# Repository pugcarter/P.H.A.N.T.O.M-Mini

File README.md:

# P.H.A.N.T.O.M-Mini

https://cad.onshape.com/documents/66c52b2957eb4a6fa7516106/w/d311932d626167deb0beda08/e/a58703558c87bdbf4c51b0a4

The P.H.A.N.T.O.M Mini is a samll ghost hunting phone P. paranormal H. Hunting A. Analize N. navigation T: Tracking O,M. Obersvation Machine me and my friends intend on going to a real hunated school Having a touchscreen with emf heartrate temp sensors I plan on maybe having detacble cameras and a walking survalnce drone with sonar and heat camera

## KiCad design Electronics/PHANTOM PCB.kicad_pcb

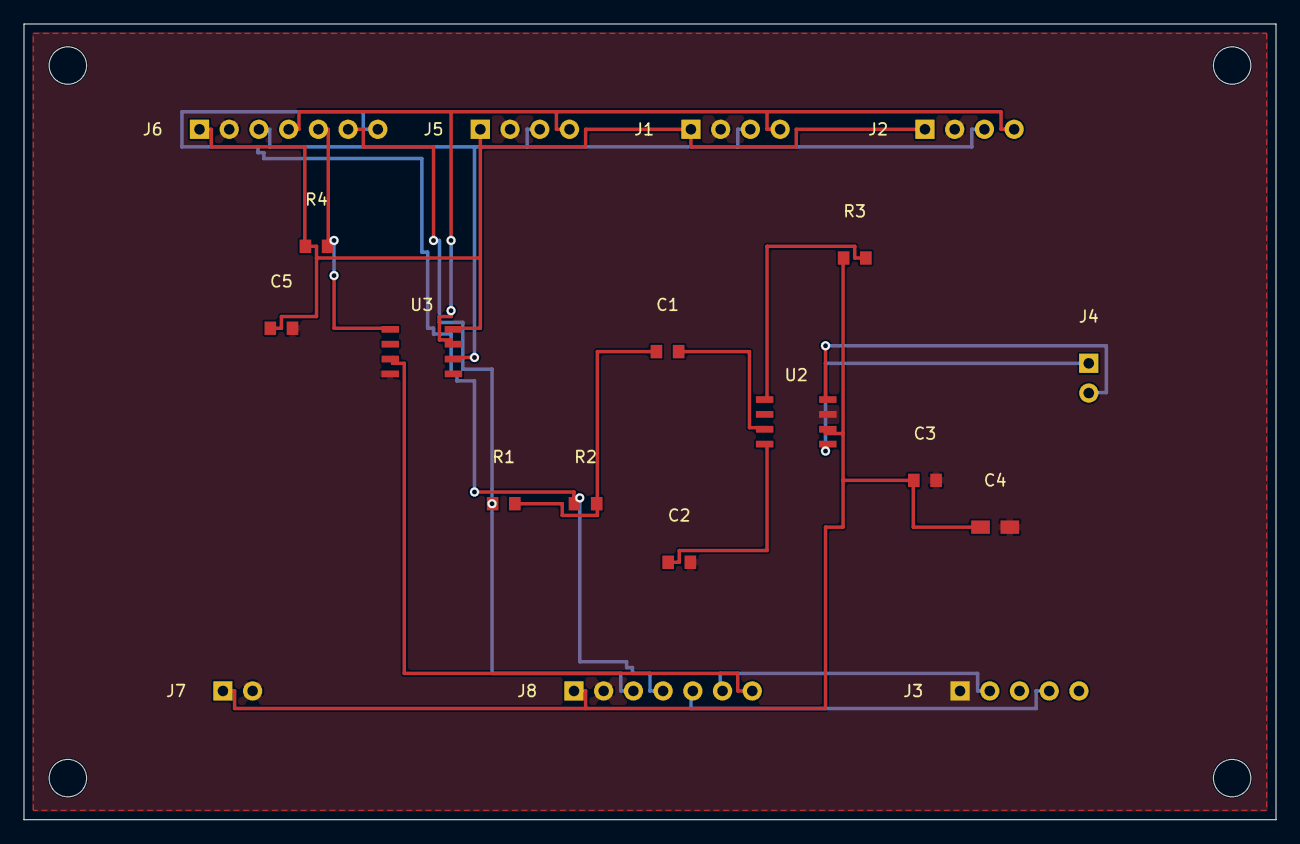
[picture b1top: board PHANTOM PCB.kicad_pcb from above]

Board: 2 copper layers, 107.0 x 68.0 mm, 23 parts (0 on the bottom side), 17 nets.

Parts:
C1, C2, C5: 100nF; Proto_C0805
C3: 1ÂµF; Proto_C0805
C4: 10ÂµF; Proto_C1206
H13.7513.55, H13.7574.45, H113.2513.55, H113.2574.45: Proto_MountingHole_M3
J1: BME280; Proto_Header_1x04_H
J2: BMM150; Proto_Header_1x04_H
J3: AudioJack3_SwitchTR; Proto_AudioAdapter_5Pin_H_GNDsolid
J4: SPEAKER; Proto_Header_1x02
J5: ESP32_I2C; Proto_Header_1x04_H
J6: SI4735_RADIO; Proto_Header_1x07_H
J7: EXT_REGULATED_3V3; Proto_Header_1x02_H
J8: HEADPHONE_AMP_MODULE; Proto_Header_1x07_H
R1, R2: 10k; Proto_R0805
R3, R4: 100k; Proto_R0805
U2: PAM8302AAD; Proto_SOIC8_U2_GNDsolid
U3: PCA9536D; Proto_SOIC8

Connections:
AMP_IN_N: C2.1, U2.4
AMP_IN_P: C1.2, U2.3
AMP_SD: R3.2, U2.1
AUDIO_3V3: C3.1, C4.1, J7.1, J8.1, R3.1, U2.6
GND: C2.2, C3.2, C4.2, C5.2, J1.2, J2.2, J3.S, J5.2, J6.2, J7.2, J8.2, U2.7, U3.4
HP_EN: J8.7, U3.3
HP_L: J3.T, J8.5
HP_R: J3.R, J8.6
I2C_SCL: J1.4, J2.4, J5.4, J6.4, U3.7
I2C_SDA: J1.3, J2.3, J5.3, J6.3, U3.6
I2C_VCC: C5.1, J1.1, J2.1, J5.1, J6.1, R4.1, U3.8
RADIO_L: J6.6, J8.3, R1.1
RADIO_MONO_MIX: C1.1, R1.2, R2.2
RADIO_R: J6.7, J8.4, R2.1
RADIO_RST: J6.5, R4.2, U3.1
SPK_NEG: J4.2, U2.8
SPK_POS: J4.1, U2.5
